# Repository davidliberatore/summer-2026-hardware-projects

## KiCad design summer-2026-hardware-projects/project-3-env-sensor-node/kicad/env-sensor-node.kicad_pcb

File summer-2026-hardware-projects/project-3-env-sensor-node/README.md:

# PCB Environmental Sensor Node

A custom-fabricated, two-layer PCB built around an ATmega328P microcontroller that reads live temperature and humidity data from a DHT22 sensor and displays it on an SSD1306 OLED over I2C.

This is Project 3 of a self-directed summer hardware roadmap (see the [main roadmap](../README.md) for Projects 1 and 2) — three ground-up analog and embedded builds completed June–September 2026 to prepare for co-op interviews.

## Overview

| | |
|---|---|
| **MCU** | ATmega328P-PU (DIP-28, socketed) |
| **Sensor** | DHT22 (temperature + humidity) |
| **Display** | SSD1306 128×64 OLED (I2C) |
| **Power** | 9V barrel jack → L7805 linear regulator → 5V rail |
| **Clock** | 16MHz external crystal |
| **Programming** | ISP via 6-pin AVR-ISP header (Arduino as ISP) |
| **Fabrication** | JLCPCB, 2-layer, 70×90mm, FR-4, HASL |
| **Design tool** | KiCad |

## Features

- Reads temperature and humidity from a DHT22 every 2 seconds
- Displays live sensor readings on an onboard OLED via I2C
- Fully self-contained once flashed — no dependency on a host computer or programmer board during normal operation
- ATmega328P is socketed (not soldered direct), so the chip can be pulled and reprogrammed or swapped

## Repo contents

```
firmware/           Arduino sketch (DHT22 + OLED sensor loop)
kicad/               Schematic + PCB layout source files
gerbers/             Fabrication files as submitted to JLCPCB
images/              Build photos, schematic screenshots
```

## Build process

1. **Schematic design (KiCad)** — power regulation (barrel jack → L7805 → decoupling), 16MHz crystal oscillator with load caps, ATmega328P with ICSP header, DHT22 with pull-up resistor, SSD1306 OLED on I2C. ERC/DRC clean with zero errors.
2. **PCB layout** — zone-based placement (power stage / MCU + crystal / edge I/O), full 2-layer routing with vias, net-by-net verification against physical module silkscreens before routing.
3. **Fabrication** — Gerbers generated and submitted to JLCPCB.
4. **Assembly** — hand-soldered all components: DIP-28 socket, crystal, ceramic and electrolytic caps, resistors, ICSP header, voltage regulator, barrel jack, DHT22, and OLED.
5. **Bring-up** — visual inspection and continuity testing before first power-on; confirmed 5V rail with the ATmega socket empty before seating the chip.
6. **Programming** — flashed via Arduino-as-ISP (Elegoo Uno running the ArduinoISP sketch, wired to the board's 6-pin ICSP header).

## v1 → v2 design fixes

An initial board revision (v1) was fabricated and used as a practice/verification board before the final order:

- **DC barrel jack footprint** was rotated inward relative to the board edge — corrected in v2's layout.
- **AREF was incorrectly tied directly to the +5V rail.** Fixed in v2 to route AREF through a GND-side decoupling cap only, avoiding potential damage if `analogReference(INTERNAL)` is ever called in firmware.

## Debugging notes

The most interesting issue during bring-up wasn't a soldering defect — it was a firmware/configuration problem that looked like a wiring problem.

**Symptom:** ISP programming repeatedly failed with sync errors (`protocol expects OK byte 0x10 but got 0x14`). Wiring, continuity, and power all checked out clean.

**Diagnosis:** Uploaded a simple Blink sketch via ISP and timed it — the LED blinked roughly 8x slower than the coded 1-second delay. This indicated the ATmega328P was running on its internal 8MHz oscillator (further divided by the default CKDIV8 fuse, to ~1MHz) rather than the board's external 16MHz crystal.

**Fix:** Ran `Tools → Burn Bootloader` over the existing ISP connection (Board: Arduino Uno, Programmer: Arduino as ISP) to rewrite the fuse bits for the external crystal, then reflashed the sensor firmware.

**Why this mattered specifically for the DHT22:** I2C (used by the OLED) tolerates a fair amount of clock deviation and worked fine even at the wrong speed. The DHT22 protocol, by contrast, is bit-banged with strict microsecond-level pulse timing — running at the wrong clock silently broke it, returning `NaN` on every read even though the rest of the board appeared to work correctly. This made the DHT22-only failure a strong clue pointing at timing rather than wiring.

A secondary issue encountered along the way: newer Arduino IDE versions auto-reset the Uno on connection, which interrupts ArduinoISP mid-handshake. Fixed with a 10µF capacitor between the Uno's physical RESET pin and GND during programming (removed when re-flashing ArduinoISP itself onto the Uno, since it blocks that upload too).

## Known limitation / future revision

The OLED footprint (J4) didn't leave clearance for the display to sit flush while keeping the ATmega socket-removable — the display module's physical footprint is larger than its 4-pin connector suggested. Solved for this board by directly soldering the OLED at a slight angle to clear the socket. A cleaner fix for a future revision: elevate the OLED on female header standoffs, or shift the J4 footprint further from the IC socket in layout.

## Results

Confirmed stable live readings on the assembled board: ~24.5°C, ~52–53% relative humidity.

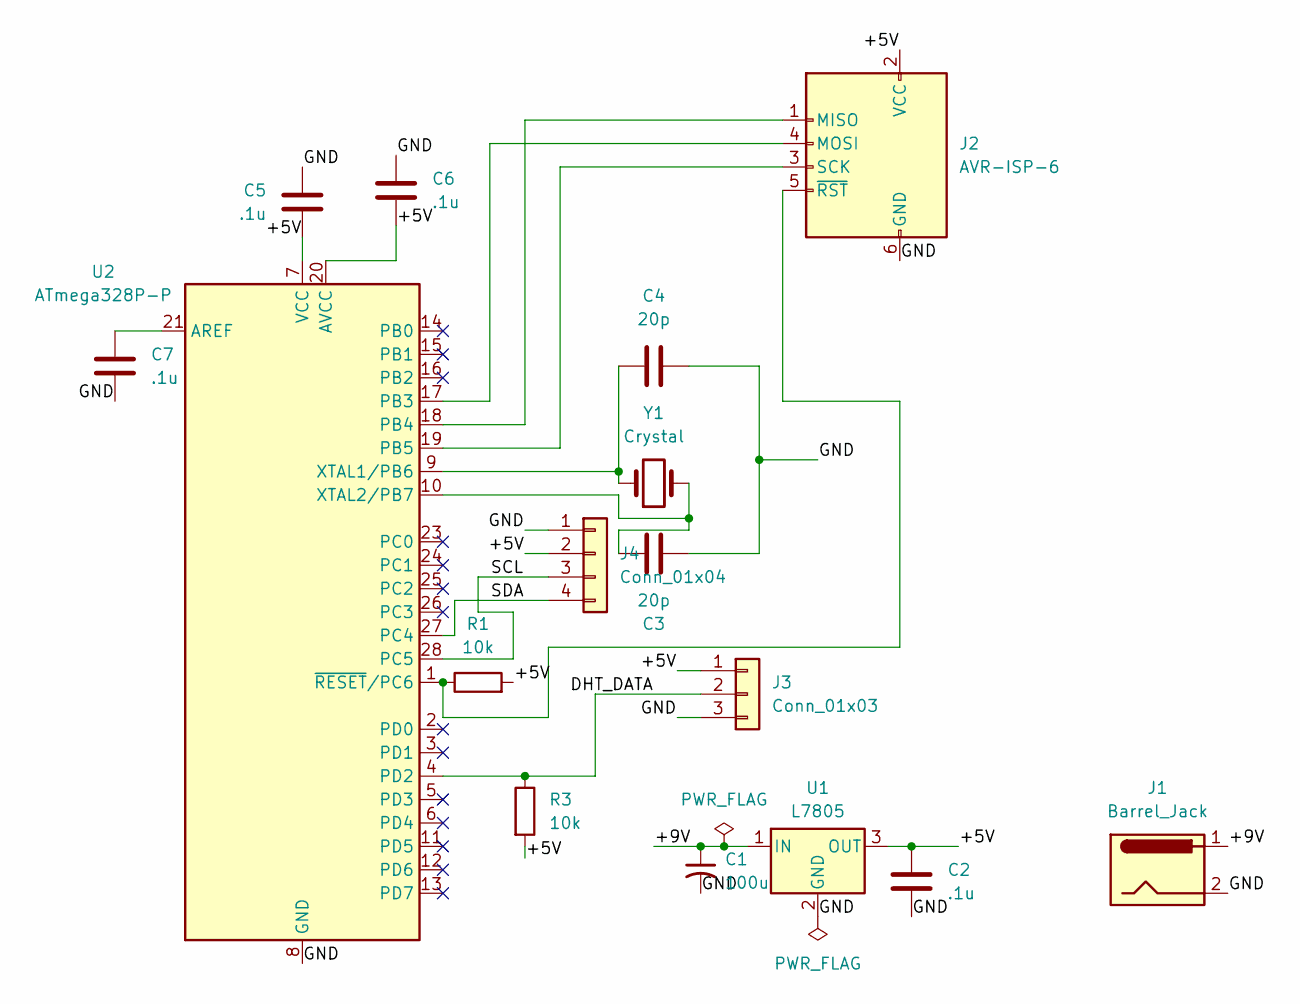
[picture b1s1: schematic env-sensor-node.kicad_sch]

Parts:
C1: 100u; CP_Radial_D5.0mm_P2.00mm
C2, C5, C6, C7: .1u; C_Disc_D5.0mm_W2.5mm_P5.00mm
C3, C4: 20p; C_Disc_D5.0mm_W2.5mm_P5.00mm
J1: Barrel_Jack; BarrelJack_CUI_PJ-063AH_Horizontal
J2: AVR-ISP-6; PinHeader_2x03_P2.54mm_Vertical
J3: Conn_01x03; PinHeader_1x03_P2.54mm_Vertical
J4: Conn_01x04; PinHeader_1x04_P2.54mm_Vertical
R1, R3: 10k; R_Axial_DIN0207_L6.3mm_D2.5mm_P10.16mm_Horizontal
U1: L7805; TO-220-3_Vertical
U2: ATmega328P-P; DIP-28_W7.62mm
Y1: Crystal; Crystal_HC49-4H_Vertical

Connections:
/+5V: C2.1, C5.2, C6.2, J2.2 (VCC), J3.1, J4.2, R1.2, R3.2, U1.3 (OUT), U2.7 (VCC), U2.20 (AVCC)
/+9V: C1.1, J1.1, U1.1 (IN)
/DHT_DATA: J3.2, R3.1, U2.4 (PD2)
/GND: C1.2, C2.2, C3.2, C4.2, C5.1, C6.1, C7.2, J1.2, J2.6 (GND), J3.3, J4.1, U1.2 (GND), U2.8 (GND), U2.22 (GND)
/SCL: J4.3, U2.28 (PC5)
/SDA: J4.4, U2.27 (PC4)
unnamed: J2.1 (MISO), U2.18 (PB4)
unnamed: J2.4 (MOSI), U2.17 (PB3)
unnamed: J2.3 (SCK), U2.19 (PB5)
unnamed: J2.5 (~RST), R1.1, U2.1 (~RESET/PC6)
unnamed: C7.1, U2.21 (AREF)
unnamed: C4.1, U2.9 (XTAL1/PB6), Y1.1
unnamed: C3.1, U2.10 (XTAL2/PB7), Y1.2

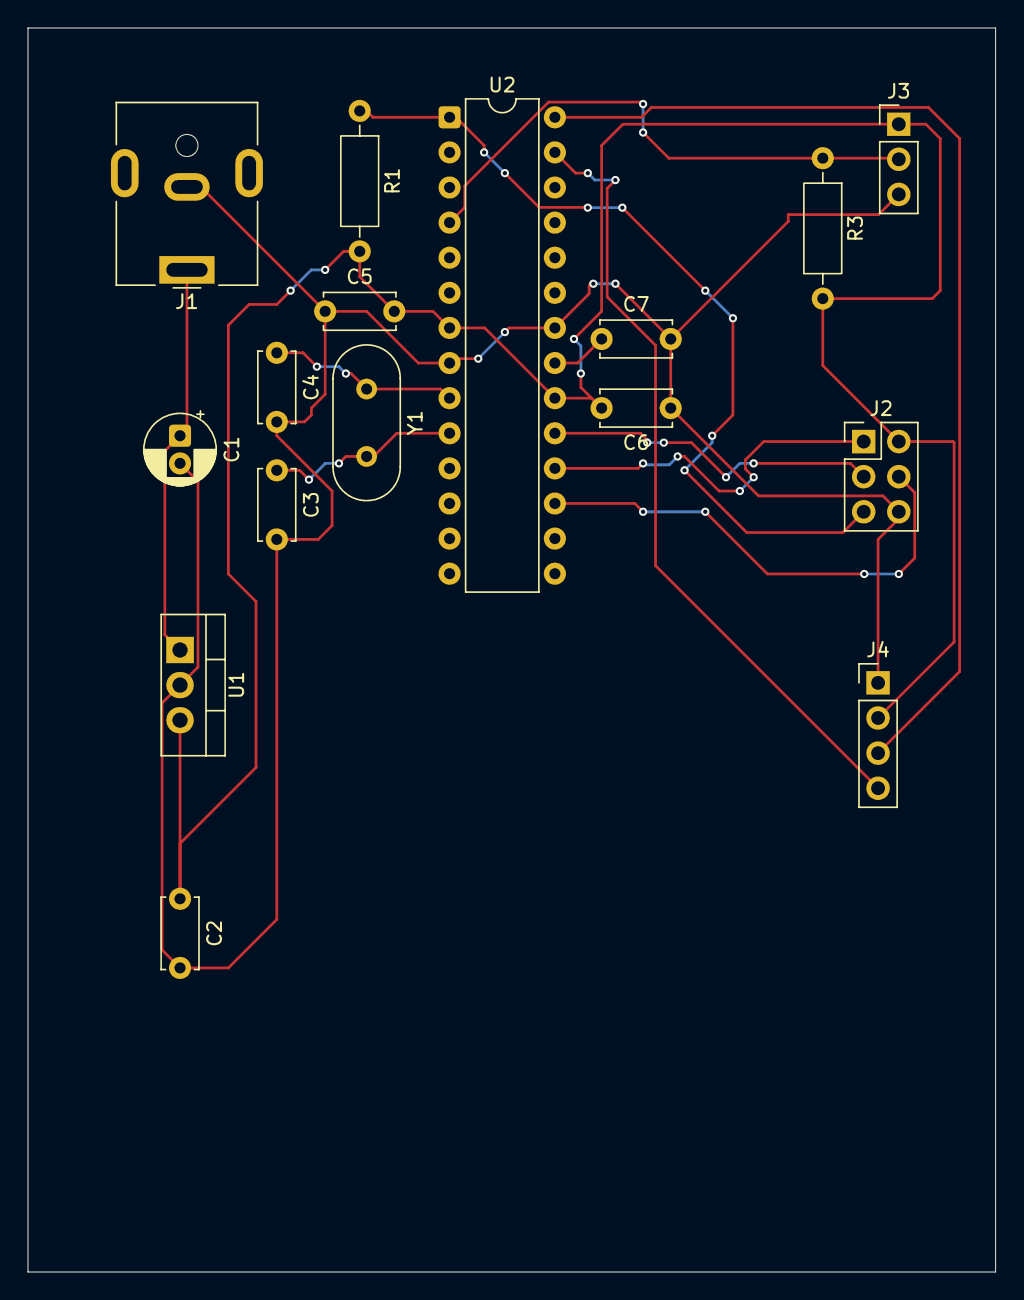
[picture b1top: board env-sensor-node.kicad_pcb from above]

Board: 2 copper layers, 70.0 x 90.0 mm, 16 parts (0 on the bottom side), 13 nets.
